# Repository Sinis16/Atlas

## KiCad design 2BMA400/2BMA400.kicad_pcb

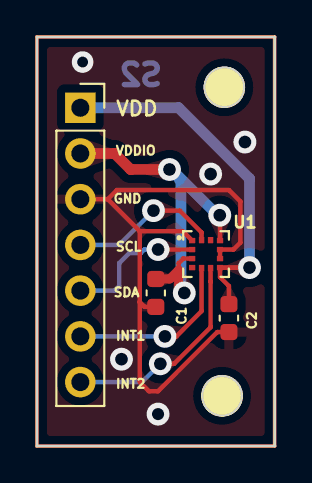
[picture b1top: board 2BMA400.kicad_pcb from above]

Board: 2 copper layers, 13.2 x 22.7 mm, 4 parts (0 on the bottom side), 7 nets.

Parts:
C1, C2: 100nF; C_0603_1608Metric
J1: Conn_01x07; PinSocket_1x07_P2.54mm_Vertical
U1: BMA400; XDCR_BMA400

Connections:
GND: C1.2, C2.2, J1.3, U1.1 (SDO), U1.8 (GNDIO), U1.9 (GND)
INT1: J1.6, U1.5 (INT1)
INT2: J1.7, U1.6 (INT2)
SCL: J1.4, U1.12 (SCX)
SDA: J1.5, U1.2 (SDX)
VDD: C2.1, J1.1, U1.7 (VDD)
VDDIO: C1.1, J1.2, U1.3 (VDDIO), U1.10 (~CSB)

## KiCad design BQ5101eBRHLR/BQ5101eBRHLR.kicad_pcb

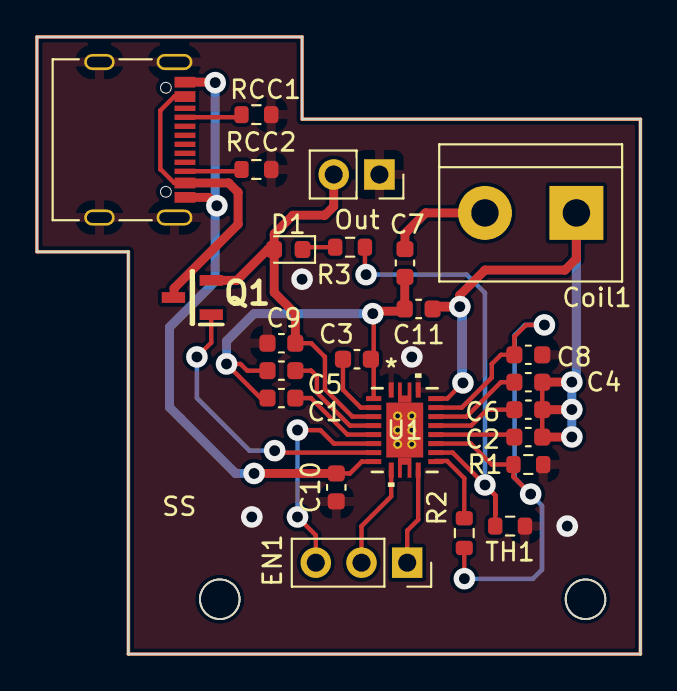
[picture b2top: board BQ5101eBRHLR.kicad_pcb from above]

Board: 2 copper layers, 33.5 x 34.3 mm, 24 parts (0 on the bottom side), 23 nets.

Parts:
C1, C2, C3, C4, C5, C6, C7, C8, C9, C10, C11: C; C_0603_1608Metric
Coil1: TerminalBlock_bornier-2_P5.08mm
D1: LED; LED_0603_1608Metric
EN1: Conn_01x03; PinSocket_1x03_P2.54mm_Vertical
J3: USB_C_Receptacle_USB2.0; USB_C_Receptacle_Palconn_UTC16-G
Out: Conn_01x02_Socket; PinSocket_1x02_P2.54mm_Vertical
Q1: SQ2361CES-T1_GE3; SOT95P237X112-3N
R1, R2, R3: R; R_0603_1608Metric
RCC1, RCC2: 5.1k; R_0603_1608Metric
TH1: Thermistor_NTC; R_0603_1608Metric
U1: BQ51013BRHLR; BQ5101eBRHLR

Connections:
AC1: C1.2, C3.2, C5.2, C7.2, C11.2, U1.2 (AC1)
AC2: C2.2, C4.2, C6.2, C11.1, Coil1.1, U1.19 (AC2)
FOD: C8.1, R1.1, R2.1, U1.14 (FOD), U1.18 (RECT)
GND: C8.2, C9.2, C10.1, J3.S1 (SHIELD), Out.1, R1.2, RCC1.1, RCC2.1, TH1.1, U1.1 (PGND), U1.20 (PGND)
unnamed: C7.1, Coil1.2
unnamed: D1.1 (K), R3.1
unnamed: EN1.1, U1.11 (EN2)
unnamed: EN1.2, U1.10 (EN1)
unnamed: EN1.3, U1.7 (*CHG)
unnamed: J3.A5 (CC1), RCC1.2
unnamed: J3.B5 (CC2), RCC2.2
unnamed: J3.A4 (VBUS), J3.A9 (VBUS), J3.B4 (VBUS), J3.B9 (VBUS), Q1.3 (D)
unnamed: Q1.1 (G), U1.8 (*AD-EN)
unnamed: C10.2, J3.A1 (GND), J3.A12 (GND), J3.B1 (GND), J3.B12 (GND), U1.9 (AD)
unnamed: C3.1, U1.3 (BOOT1)
unnamed: C4.1, U1.17 (BOOT2)
unnamed: C5.1, U1.5 (CLMP1)
unnamed: C6.1, U1.16 (CLMP2)
unnamed: C1.1, U1.6 (COM1)
unnamed: C2.1, U1.15 (COM2)
unnamed: R2.2, U1.12 (ILIM)
unnamed: R3.2, TH1.2, U1.13 (TS-CTRL)
OUT: C9.1, D1.2 (A), Out.2, Q1.2 (S), U1.4 (OUT)
